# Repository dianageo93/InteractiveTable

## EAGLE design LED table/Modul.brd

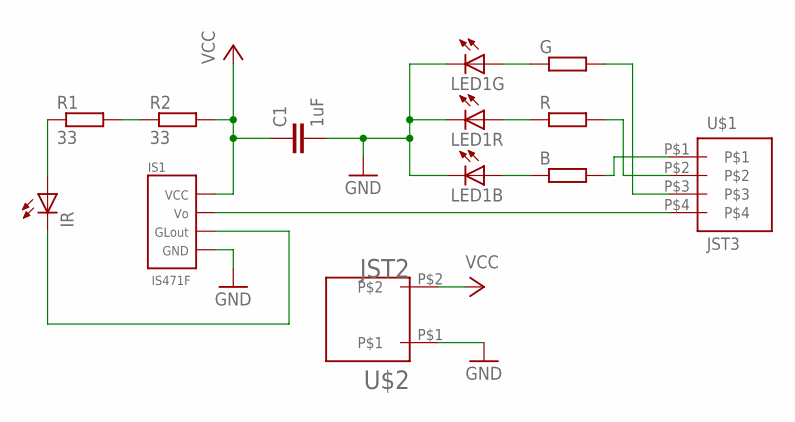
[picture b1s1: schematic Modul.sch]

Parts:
B: R-EU_R1206; R1206
C1: 1uF; C1206
G: R-EU_R1206; R1206
IR: LEDSML1206; SML1206
IS1: IS471F
LED1: LP2C63-ST-RGB-SR0
R: R-EU_R1206; R1206
R1, R2: 33; R1206
U$1: JST3; JST
U$2: JST2; JST

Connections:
GND: C1.2, IS1.P$3 (GND), LED1.4 (C), LED1.5 (C), LED1.6 (C), U$2.P$1
unnamed: R1.2, R2.1
unnamed: IR.A, R1.1
unnamed: IR.C, IS1.P$4 (GL)
unnamed: IS1.P$2 (VO), U$1.P$4
unnamed: G.1, LED1.1 (A)
unnamed: R.2, U$1.P$2
unnamed: B.2, U$1.P$1
unnamed: G.2, U$1.P$3
unnamed: LED1.2 (A), R.1
unnamed: B.1, LED1.3 (A)
VCC: C1.1, IS1.P$1 (VCC), R2.2, U$2.P$2

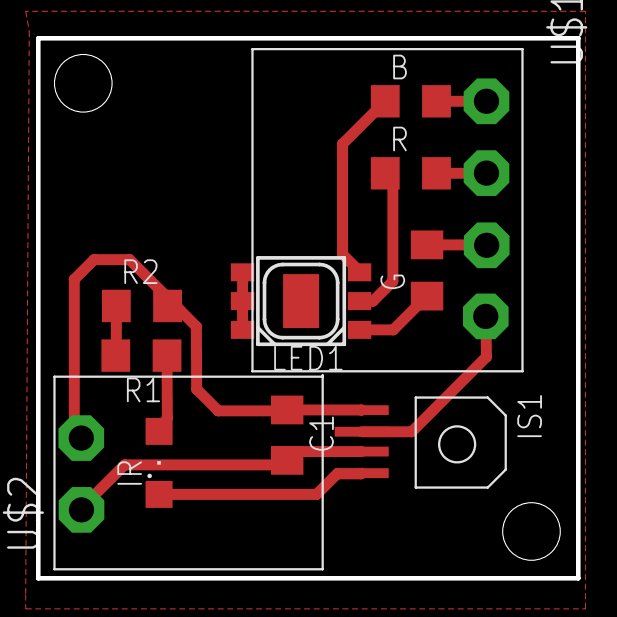
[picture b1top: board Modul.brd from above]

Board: 2 copper layers, 30.0 x 30.0 mm, 11 parts (0 on the bottom side), 12 nets.
